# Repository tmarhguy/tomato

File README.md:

<h1 align="center">Tomato</h1>
<p align="center"><strong>A 32-bit computer architecture built from copper to browser.</strong></p>
<p align="center">

</p>

<p align="center">

</p>
<p align="center"><em>Physical ALU slice · <a href="web/assets/os/tomato-demo-os.mp4">FPGA Tomato OS recording (4× preview)</a></em></p>

The animation is a sped-up preview of the complete FPGA machine.

Tomato is one architecture expressed at several layers:

- a fabricated and soldered **8-bit 74xx Dual-LUT ALU slice**;
- a complete **FPGA Tomato** on the Nexys A7-100T that boots the
  assembly-written Tomato OS;
- **TOMATO OS v3.0**, written in Tomato assembly, with 14 menu entries;
- a functional **Virtual Tomato** ISA emulator in the browser;
- editable Digital schematics, KiCad boards, RTL, an assembler, and focused verification.

The complete discrete computer remains a goal. The assembled ALU slice is real
hardware, but it is not a complete discrete machine. The complete running
computer in this repository is the FPGA implementation.

**Explore:** [architecture](docs/architecture.md) ·
[current status](docs/status.md) ·
[Tomato OS](software/os/README.md) ·
[ISA](docs/isa/README.md) ·
[compute](docs/compute.md) ·
[documentation index](docs/README.md) ·
[project site](https://tomato.tmarhguy.com/)

## Architecture at a glance

These curated diagrams explain the system; the
[interactive GitDiagram](https://gitdiagram.com/tmarhguy/tomato) provides a
zoomable, generated map of the public repository's default branch.

**Visual entry points:** [interactive repository map](https://gitdiagram.com/tmarhguy/tomato) ·
[architecture guide](docs/architecture.md) ·
[web architecture](https://tomato.tmarhguy.com/architecture.html) ·
[ISA reference](https://tomato.tmarhguy.com/isa.html) ·
[run Virtual Tomato](https://tomato.tmarhguy.com/virtual.html)

### One architecture, several realizations

<picture>
  <source media="(prefers-color-scheme: dark)" srcset="web/assets/gallery/diagrams/system-realizations-dark.svg">
  
</picture>

The four realization boxes are deliberately separate. The assembled discrete
hardware proves the ALU slice; the FPGA is the complete machine; Icarus runs
the RTL locally; and the browser is a functional ISA emulator.
[Diagram source](docs/diagrams/system-realizations.mmd).

### From source files to runnable artifacts

<picture>
  <source media="(prefers-color-scheme: dark)" srcset="web/assets/gallery/diagrams/artifact-pipeline-dark.svg">
  
</picture>

The generated FPGA burn and browser image share the same OS and control data.
They do not share an execution engine: the FPGA and Icarus execute Verilog,
while `tomato-cpu.js` mirrors the ISA-level behavior in JavaScript.
[Diagram source](docs/diagrams/artifact-pipeline.mmd).

### Inside FPGA Tomato

<picture>
  <source media="(prefers-color-scheme: dark)" srcset="web/assets/gallery/diagrams/fpga-datapath-dark.svg">
  
</picture>

The board harness owns clocks, pins, keypad debounce, glyph rendering, DVI, and
seven-segment output. The machine core exposes those facilities as ports and
memory-mapped windows, keeping board-specific wiring outside the CPU RTL.
[Diagram source](docs/diagrams/fpga-datapath.mmd).

### Authority and state boundaries

- **Edit:** Digital schematics, ISA CSVs, assembly sources, and FPGA/browser
  implementation source.
- **Regenerate:** `.mem` images, `rtl/burn/*.vh`, `tomato-os.bin`, and
  bitstreams. These are derived artifacts, not design authorities.
- **Runtime state:** FPGA RAM, registers, framebuffer, compiler, radio mailbox,
  and the browser machine are volatile. Reset or reload restores the compiled
  image; this repository has no application database.
- **External systems:** Envelop clients, durable queues, hosted services, and
  the nearby bridge belong to the separate Envelop project.

## What runs now

| Layer | Current, repository-backed statement |
|---|---|
| Architecture | 32-bit datapath and instruction word |
| ALU | Custom three-source Dual-LUT ALU: two LUT3 functions feed an adder, `f(a,b,c) + g(a,b,c) + carry` |
| ISA | **91 instructions plus NOP, 92 burned rows** in a 512-row control ROM |
| Register array | Discrete (primary): **32,768 × 32-bit**. FPGA: **256 × 32-bit**, addressed as 3 bank bits plus a 5-bit register field; `r0` is hardwired to zero — no space for more on that implementation |
| FPGA | 100 MHz board input; **6.25 MHz** default CPU and 25 MHz pixel clocks; 90 MHz is only the nextpnr timing target |
| OS | The complete FPGA computer boots assembly-written **TOMATO OS v3.0**, with 14 menu entries including Envelop |
| Browser | Functional ISA-level emulation; not cycle-accurate RTL or physical execution |
| Hardware compiler | Counter FSM searches all **65,536 LUT pairs** for one fixed A/B/C/carry/output example; a hit verifies that example, not a general function |
| ALU verification | A **130-billion-vector** 32-bit ALU run is recorded and its harness is reproducible; the full run log is not checked in |

The architectural register count is **32,768**, because discrete is the
superior design constraint. FPGA implementation remains **256 × 32-bit**
because there is no space for a larger file; its 3-read/1-write array maps to
distributed RAM. Discrete uses external SRAM plus a seven-bit superbank and
`SETBANK2`. Neither the superbank nor that instruction exists in the current
FPGA RTL and burned ISA.

For evidence paths and the distinction between source-complete,
hardware-dependent, and deployed behavior, use
[`docs/status.md`](docs/status.md). Historical journal entries can describe
earlier designs and counts; they do not override current sources.

## See it, run it, inspect it

### Browser

Open the [Tomato site](https://tomato.tmarhguy.com/) and choose the Virtual
Tomato experience. Its checked-in OS image is generated from the assembly and
control data in this repository. Results there must be labeled virtual.

<p align="center">
  
</p>
<p align="center"><strong><a href="https://tomato.tmarhguy.com/virtual.html">Play with Virtual Tomato →</a></strong><br><em>Functional ISA emulation with simulated peripherals—not FPGA or discrete-hardware execution.</em></p>

### Local RTL simulation

Icarus Verilog can boot the OS and print its framebuffer without an FPGA:

```bash
make -C hardware/fpga/core os
```

Run the focused core regression:

```bash
make -C hardware/fpga/core test
```

These commands prove simulation behavior, not a currently programmed board.

### Assemble a Tomato program

```bash
python3 software/assembler.py software/asm/counter.s \
  -o /tmp/counter.mem --list
python3 software/assembler.py --selftest
```

The assembler reads the burned ISA and pseudo-instruction CSVs rather than
carrying a private opcode table.

### FPGA build

The default flow is Yosys → nextpnr-xilinx → Project X-Ray. An optional Linux
Vivado batch target is also provided. Building a bitstream does not prove that
a board is currently programmed.

```bash
make fpga-setup
make fpga
```

Programming is intentionally a separate, hardware-changing action; see
[`hardware/fpga/README.md`](hardware/fpga/README.md).

## Proof across the stack

<table>
  <tr>
    <td width="33%" align="center" valign="middle"></td>
    <td width="33%" align="center" valign="middle"></td>
    <td width="33%" align="center" valign="middle"></td>
  </tr>
</table>

- **Physical scope:** [`hardware/kicad/boards/07_alu/`](hardware/kicad/boards/07_alu/)
- **Editable logic:** [`hardware/digital/`](hardware/digital/)
- **Complete FPGA machine:** [`hardware/fpga/core/`](hardware/fpga/core/)
- **Machine software:** [`software/`](software/)
- **Verification:** [`verification/`](verification/)
- **Evidence and asset provenance:** [`docs/assets.md`](docs/assets.md)

## Envelop and compute

Envelop is a separate messaging project. Its Tomato-side client and bounded
compute executor are linked into Tomato OS; its user clients, backend, and
nearby bridge live outside this repository.

The intended hardware message path is:

`person → Envelop web app → backend queue → nearby verified bridge → Envelop in Tomato OS → Tomato CPU → labeled reply`

<picture>
  <source media="(prefers-color-scheme: dark)" srcset="web/assets/gallery/diagrams/envelop-boundary-dark.svg">
  
</picture>

Source in a repository is not evidence that a bridge is active or that a reply
ran on hardware. Bridge software is available in the separate Envelop project,
but a nearby authenticated bridge and completed FPGA job require live evidence.
Virtual previews are explicit, separate, and labeled. See
[`docs/compute.md`](docs/compute.md) for the current boundary.
[Diagram source](docs/diagrams/envelop-boundary.mmd).

## Repository map

| Path | Purpose |
|---|---|
| [`docs/`](docs/) | Canonical guides, ISA contracts, and historical journal |
| [`hardware/digital/`](hardware/digital/) | Editable architecture schematics |
| [`hardware/kicad/`](hardware/kicad/) | PCB designs and assembly records |
| [`hardware/fpga/`](hardware/fpga/) | Complete machine, board harness, and simulation |
| [`software/`](software/) | Assembler, programs, and Tomato OS |
| [`microcode/`](microcode/) | Control-ROM packaging |
| [`verification/`](verification/) | ALU and implementation checks |
| [`web/`](web/) | Project site and browser emulator |

## Documentation and history

Start with [`docs/README.md`](docs/README.md). It separates current canonical
guidance from the dated [`docs/log/`](docs/log/) engineering record. The
journal preserves decisions, wrong turns, and superseded designs as history;
use the [current journal index](docs/log/README.md) to navigate it.

Documentation authority and terminology are defined in
[`docs/documentation-policy.md`](docs/documentation-policy.md). When prose and
executable sources disagree, that policy determines which source wins.

## Documentation

Detailed architecture, implementation, verification, and technical
documentation is available in the project documentation.
The technical reference manual source is [`docs/index.adoc`](docs/index.adoc);
build the static manual locally with `make docs` (requires Asciidoctor).

## License and author

Tomato is licensed under the [Solderpad Hardware License 2.1](LICENSE).
Architecture and project by **Tyrone Marhguy**, Computer Engineering ’28,
University of Pennsylvania.

[Contributing](CONTRIBUTING.md) · [security](SECURITY.md) ·
[citation](CITATION.cff) · [third-party notices](THIRD_PARTY_NOTICES.md)

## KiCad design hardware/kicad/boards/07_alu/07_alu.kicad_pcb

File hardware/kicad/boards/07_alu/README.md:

# 07 — Dual-LUT ALU PCB

The physical **32-bit ALU** for Tomato — two independent 3-input LUT planes per bit, summed through **74ACT283** nibble adders, with on-board flag logic, carry select, and a bring-up LED wall. One PCB is an **8-bit slice**; stack two for 16-bit bench bring-up. Digital source of truth: [alu-32b-final.dig](../../../digital/modules/alu-32b-final.dig). KiCad project: [07_alu.kicad_pro](07_alu.kicad_pro).

<p align="center"><em>Lot 07 in the round &amp; on the iron · Dual-LUT slice</em></p>

---

## Table of Contents

- [At a glance](#at-a-glance)
- [Efficiency metrics](#efficiency-metrics)
- [Hierarchy](#hierarchy)
- [Schematics](#schematics)
- [PCB layout](#pcb-layout)
- [Bill of materials](#bill-of-materials)
- [I/O and bring-up](#io-and-bring-up)
- [Project files](#project-files)
- [Related docs](#related-docs)

---

## At a glance

```
alu_out[n] = ( lutA(a,b,c) + lutB(a,b,c) + cin ) & 1   per bit, ripple across nibbles
```

| Item | Detail |
|------|--------|
| Board | `07_alu` — modular 74xx ALU (not the legacy 270mm transistor `01_alu`) |
| Topology | `alu_1b_X` + `alu_1b_Y` → `alu_4b` × 2 (ripple carry) → 8b slice on PCB |
| Key ICs | **74ACT151** (LUT3 mux), **74ACT283** (4b adder), **74HCT688** (zero detect), **74ACT377** (flag reg), **74ACT541** (buffer) |
| Outline | **99.95 × 99.80 mm** ≈ **9975 mm²** (Edge.Cuts) |
| Density | **25 logic ICs / 8b** → **3.125 IC/bit**, **≈1247 mm²/bit** |
| Layout | Routed — **0 unrouted** nets (see status below) |
| Silk | Tomato ALU branding, UPenn / author contact on copper |

*Figure 1 — `07_alu` board render — `CELL 0` / `CELL 1`, flag logic, opcode/operand LED wall, I/O headers.*

*Figure 2 — Top copper — routed cells, flag block, silkscreen.*

---

## Efficiency metrics

| Metric | Value | Notes |
|--------|-------|-------|
| Board area | **99.95 × 99.80 mm** ≈ **9975 mm²** | Edge.Cuts bbox |
| Logic ICs (8b) | **25** | 17×151 + 2×283 + 2×00 + 1×86 + 1×377 + 1×541 + 1×688 |
| IC / bit | **3.125** | 25 / 8 |
| Board mm² / bit | **≈1247** | 9975 / 8 |

Legacy hybrid ([01_alu](../01_alu/README.md)): **3488 MOSFETs / 8b = 436 T/bit**. Journal carry-bypass ≈**16.5 MHz** on discrete path.

---

## Hierarchy

The KiCad tree mirrors the Digital verification ladder:

| Sheet | Role |
|-------|------|
| [07_alu.kicad_sch](07_alu.kicad_sch) | Top — two [alu_4b](alu_4b.kicad_sch) slices, `CIN-MAIN` / `COUT-MAIN` ripple |
| [alu_4b.kicad_sch](alu_4b.kicad_sch) | Four [alu_1b_X](alu_1b_X.kicad_sch) + four [alu_1b_Y](alu_1b_Y.kicad_sch) → one **74ACT283** |
| [alu_1b_X.kicad_sch](alu_1b_X.kicad_sch) / [alu_1b_Y.kicad_sch](alu_1b_Y.kicad_sch) | Single-bit **74ACT151** LUT3 (`lutA` / `lutB` programs via opcode buses) |
| [flags_logic.kicad_sch](flags_logic.kicad_sch) | Z/N/C/V, LT/GT/GTE, **74ACT151** carry select (`CSEL`) |
| [led_unit.kicad_sch](led_unit.kicad_sch) | Opcode, flag, and A/B/C/OUT bus LEDs for bench debug |
| [iopins.kicad_sch](iopins.kicad_sch) | Connector pinout — power, operands, opcodes, control |

Full CPU width is four 8-bit slices (or eight 4-bit cells) in the larger Tomato datapath; this board implements one **8-bit bring-up slice** with the same cell geometry used in simulation.

---

## Schematics

### Top sheet — two 4-bit ALU cells

*Figure 3 — `alu_4b_0` and `alu_4b_1` chained; `flags_logic`, `led_control`, and `iopins` sheets.*

### 4-bit slice — dual LUT into adder

*Figure 4 — `alu_1b_X0–X3` and `alu_1b_Y0–Y3` feed **U3 (74ACT283)**; `cinD` / `cout` nibble carry.*

### 1-bit LUT3 (`alu_1b_Y` example)

*Figure 5 — **74ACT151** as 3-input LUT: `a,b,c` select among `ALU_OPCODE_Y0–Y7`.*

### Flag logic

*Figure 6 — Zero compare (**74HCT688**), flag register (**74ACT377**), **74ACT151** `CIN-MAIN` mux from `CSEL` + latched flags.*

### LED bring-up panel

*Figure 7 — Visualize `ALU_OPCODE_X/Y`, flags, and A/B/C/OUT buses on the bench.*

### I/O connectors

*Figure 8 — Headers for A/B/C/OUT, opcode buses, `CSEL`, `FLAG_WE`, `SYS-CLK`, power.*

---

## PCB layout

| Asset | Description |
|-------|-------------|
| [alu_8b_board.webp](../../../../web/assets/pcb/alu_8b_board.webp) | Board render — assembled view, silk, LED wall |
| [alu_8b_pcb.jpg](../../../../web/assets/pcb/alu_8b_pcb.jpg) | 2D layout — top copper, cells, flag block |
| [status-bar.webp](../../../../web/assets/pcb/status-bar.webp) | Route status — **717 pads**, **358 vias**, **2405** segments, **185 nets**, **0 unrouted** |
| [drc.webp](../../../../web/assets/pcb/drc.webp) | Design Rules Check — **0 violations**, **0 unconnected** |

*Figure 9 — KiCad status bar — fully routed, fab-ready.*

*Figure 10 — DRC pass — no violations, no unconnected items.*

---

## Bill of materials

Each board is **131 placements** — mostly SOIC logic, a wall of 0805 LEDs, and a handful of through-hole resistor networks and headers. The tables below list **one board**; double quantities for a two-board 16-bit build.

### Integrated circuits

| Qty | Value | MPN (ordered) | Digi-Key | Role |
|-----|-------|---------------|----------|------|
| 17 | 74ACT151 | CD74ACT151M96 | [296-12766-1-ND](https://www.digikey.com/en/products/detail/texas-instruments/CD74ACT151M96/12766) | 8:1 mux — LUT3 planes in both cells + flag `CSEL` |
| 2 | 74ACT283 | CD74ACT283M | [296-32996-5-ND](https://www.digikey.com/en/products/detail/texas-instruments/CD74ACT283M/32996) | 4-bit ripple adder — one per nibble cell |
| 2 | 74ACT00 | SN74ACT00DR | [296-14690-1-ND](https://www.digikey.com/en/products/detail/texas-instruments/SN74ACT00DR/14690) | Quad NAND — glue in flag logic |
| 1 | 74ACT86 | SN74ACT86DR | [296-9757-1-ND](https://www.digikey.com/en/products/detail/texas-instruments/SN74ACT86DR/9757) | Quad XOR — flag compare |
| 1 | 74ACT377 | MC74ACT377DWR2G | [MC74ACT377DWR2GOSCT-ND](https://www.digikey.com/en/products/detail/onsemi/MC74ACT377DWR2G/377) | Octal D-FF — flag latch (U40) |
| 1 | 74ACT541 | CD74ACT541M96 | [296-14501-1-ND](https://www.digikey.com/en/products/detail/texas-instruments/CD74ACT541M96/14501) | Octal bus buffer (U1) |
| 1 | 74HC688 | CD74HCT688M96 | [296-24357-1-ND](https://www.digikey.com/en/products/detail/texas-instruments/CD74HCT688M96/24357) | 8-bit identity comparator — zero detect (U4); **HCT** for 5V ACT inputs |

### Passives and indicators

| Qty | Value | MPN (ordered) | Digi-Key | Footprint | Refs |
|-----|-------|---------------|----------|-----------|------|
| 25 | 100nF | CC0603KRX7R9BB104 | [311-1344-1-ND](https://www.digikey.com/en/products/detail/yageo/CC0603KRX7R9BB104/311) | 0603 | C3, C4, C16, C36–C59 |
| 63 | Red LED | LTST-C170KRKT | [160-1415-1-ND](https://www.digikey.com/en/products/detail/lite-on-inc/LTST-C170KRKT/160) | 0805 | D4–D71 |
| 7 | 470Ω bussed | 4610X-101-471LF | [4610X-1-471LF-ND](https://www.digikey.com/en/products/detail/bourns-inc/4610X-101-471LF/4610) | SIP-9 | RN1–RN7 |
| 2 | 470Ω bussed | 4604X-101-471LF | — | SIP-4 | RN9, RN10 |

The SIP-4 networks are **3-resistor bussed 470Ω** parts on [led_unit.kicad_sch](led_unit.kicad_sch). DigiKey often lists `4604X-101-471LF` on backorder with a high minimum — source from lab stock, or use **6× discrete 470Ω** per board (one end common, three to LED nets).

### Connectors

| Qty | Value | MPN | Refs |
|-----|-------|-----|------|
| 2 | 1×4 header | PRPC004SAAN-RC | J10, J11 |
| 7 | 1×8 header | PRPC008SAAN-RC | J5–J7, J12, J15–J17 |

Headers are standard 2.54 mm pin strips — any equivalent works.

### Ordering notes

- **DigiKey BOM (2 boards):** [`07_alu_digikey_bom.csv`](../../fabrication/07_alu/07_alu_digikey_bom.csv) — upload-ready CSV; order **`100884560`** placed Aug 2026 (~**$61** all-in for two boards).
- **Fabrication exports:** Gerbers, pick-and-place, and order receipt in [`hardware/kicad/fabrication/07_alu/`](../../fabrication/07_alu/).
- **PCBs:** JLCPCB bare boards — see [Ordered Tomato](../../../../docs/log/2026-08-07%20-%20Ordered%20Tomato.md).

---

## I/O and bring-up

From [iopins.kicad_sch](iopins.kicad_sch):

| Group | Signals |
|-------|---------|
| Operands | `A[7:0]`, `B[7:0]`, `C[7:0]` |
| Result | `OUT[7:0]` |
| LUT programs | `ALU_OPCODE_X0–X7`, `ALU_OPCODE_Y0–Y7` (8-bit truth table per LUT plane) |
| Carry select | `CSEL0–CSEL2` → `CIN-MAIN` |
| Flags | `FLAG_WE`, `ZIN`; outputs `flagZ/N/C/V`, LT/GT/GTE |
| Clock | `SYS-CLK` (flag register) |

Suggested flow: program opcode buses for a known LUT pair (e.g. add = `0x96` on both planes), wiggle operands on headers, read **OUT** on LEDs or scope — same spirit as [alu-display-control.dig](../../../digital/modules/alu-display-control.dig) on the full CPU.

---

## Project files

| File | Purpose |
|------|---------|
| [07_alu.kicad_pro](07_alu.kicad_pro) | KiCad project |
| [07_alu.kicad_sch](07_alu.kicad_sch) | Root schematic |
| [07_alu.kicad_pcb](07_alu.kicad_pcb) | PCB layout |
| [alu_1b_X.kicad_sch](alu_1b_X.kicad_sch), [alu_1b_Y.kicad_sch](alu_1b_Y.kicad_sch) | Bit slices |
| [alu_4b.kicad_sch](alu_4b.kicad_sch) | Nibble cell |
| [flags_logic.kicad_sch](flags_logic.kicad_sch), [led_unit.kicad_sch](led_unit.kicad_sch) | Status + debug |
| [iopins.kicad_sch](iopins.kicad_sch) | Connector map |
| [07_alu_digikey_bom.csv](../../fabrication/07_alu/07_alu_digikey_bom.csv) | DigiKey BOM — 2-board order |

Figures above live under [`web/assets/`](../../../../web/assets/).

---

## Related docs

| Doc | Topic |
|-----|-------|
| [Root README](../../../../README.md) | Project overview |
| [74251 carry mux log](../../../../docs/log/2026-06-26%20-%20ALU%20-%20Redesign%20with%2074251.md) | Why **74251/ACT151** over **74151** + tri-state |
| [Mode mux elimination](../../../../docs/log/2026-06-27%20-%20Elimination%20of%20Mode%20Multiplexers.md) | LUT3 feeds adder directly |
| [ALU segment display](../../../../docs/log/2026-06-19%20-%20ALU%20segment%20display%20design.md) | Display strategy on full CPU |
| [Ordered Tomato](../../../../docs/log/2026-08-07%20-%20Ordered%20Tomato.md) | PCB + parts order log |
| [First Phase of Assembly](../../../../docs/log/2026-08-18%20-%20First%20Phase%20of%20Assembly.md) | Muxes, adders, first lamps |
| [verification/README.md](../../../../verification/README.md) | Formal + UVM sign-off on Digital export |

**Author:** Tyrone Marhguy — see [Author](../../../../README.md#author) in root README.

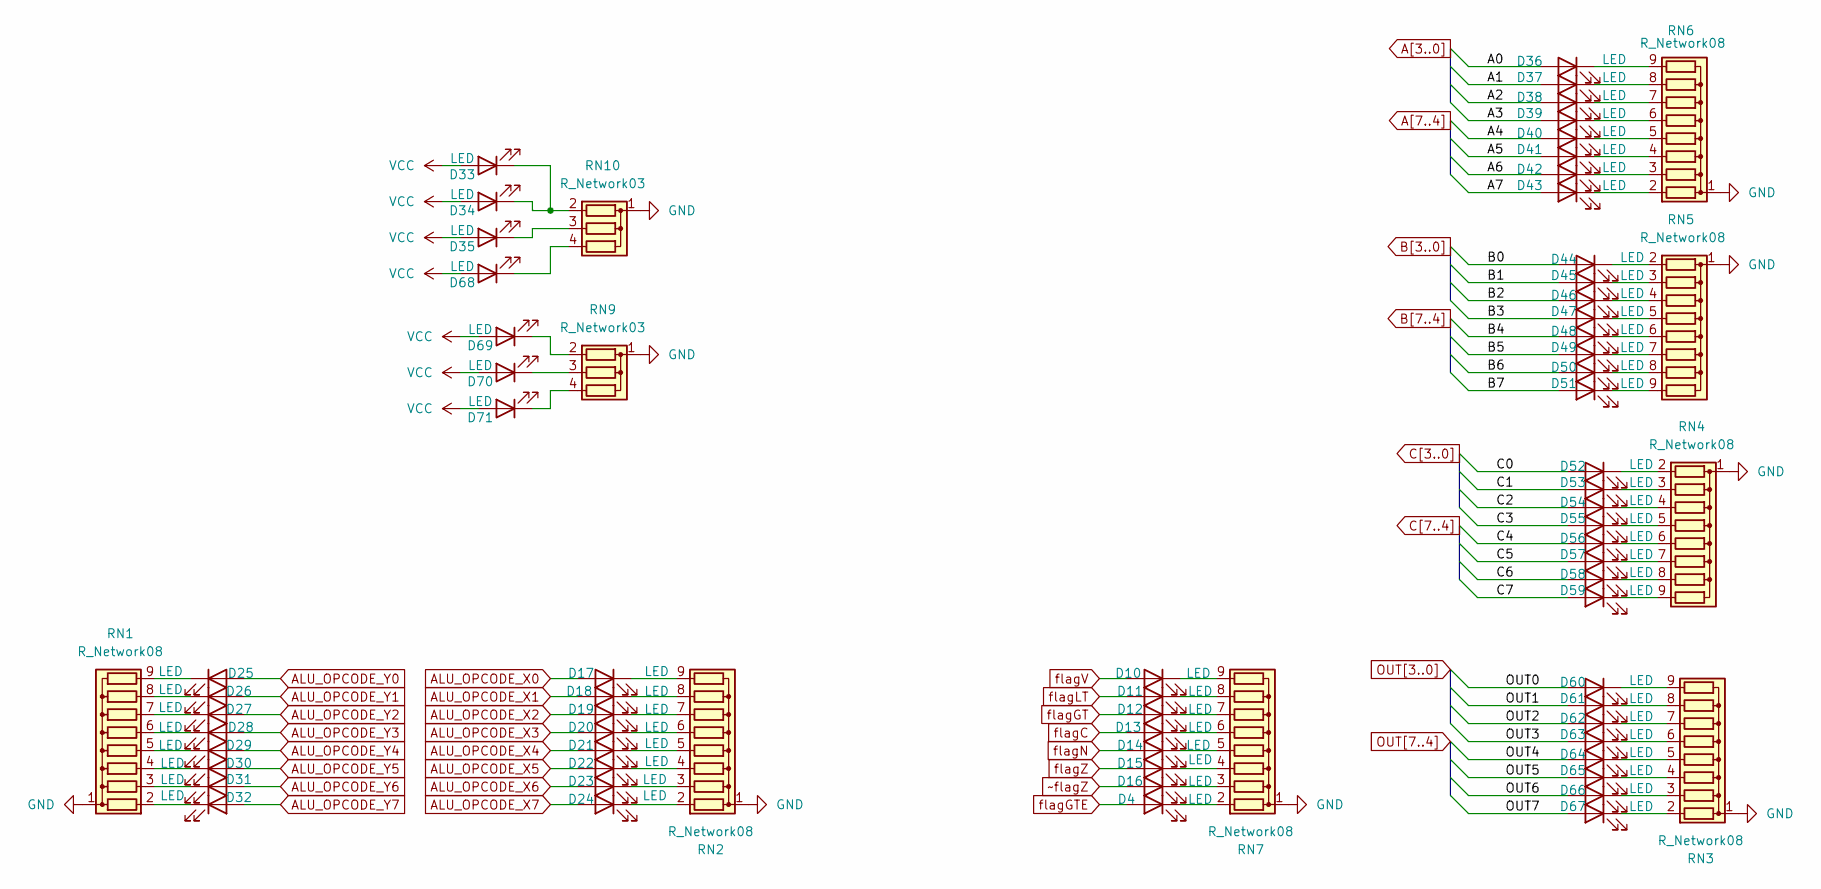
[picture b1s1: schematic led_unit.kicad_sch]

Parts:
D4, D10, D11, D12, D13, D14, D15, D16, D17, D18, D19, D20, D21, D22, D23, D24, D25, D26, D27, D28, D29, D30, D31, D32, D33, D34, D35, D36, D37, D38, D39, D40, D41, D42, D43, D44, D45, D46, D47, D48, D49, D50, D51, D52, D53, D54, D55, D56, D57, D58, D59, D60, D61, D62, D63, D64, D65, D66, D67, D68, D69, D70, D71: LED; LED_0805_2012Metric
RN1, RN2, RN3, RN4, RN5, RN6, RN7: R_Network08; R_Array_SIP9
RN9, RN10: R_Network03; R_Array_SIP4

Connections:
A0: D36.2 (A); also elsewhere on the board
A1: D37.2 (A); also elsewhere on the board
A2: D38.2 (A); also elsewhere on the board
A3: D39.2 (A); also elsewhere on the board
A4: D40.2 (A); also elsewhere on the board
A5: D41.2 (A); also elsewhere on the board
A6: D42.2 (A); also elsewhere on the board
A7: D43.2 (A); also elsewhere on the board
ALU_OPCODE_X0: D17.2 (A); also elsewhere on the board
ALU_OPCODE_X1: D18.2 (A); also elsewhere on the board
ALU_OPCODE_X2: D19.2 (A); also elsewhere on the board
ALU_OPCODE_X3: D20.2 (A); also elsewhere on the board
ALU_OPCODE_X4: D21.2 (A); also elsewhere on the board
ALU_OPCODE_X5: D22.2 (A); also elsewhere on the board
ALU_OPCODE_X6: D23.2 (A); also elsewhere on the board
ALU_OPCODE_X7: D24.2 (A); also elsewhere on the board
ALU_OPCODE_Y0: D25.2 (A); also elsewhere on the board
ALU_OPCODE_Y1: D26.2 (A); also elsewhere on the board
ALU_OPCODE_Y2: D27.2 (A); also elsewhere on the board
ALU_OPCODE_Y3: D28.2 (A); also elsewhere on the board
ALU_OPCODE_Y4: D29.2 (A); also elsewhere on the board
ALU_OPCODE_Y5: D30.2 (A); also elsewhere on the board
ALU_OPCODE_Y6: D31.2 (A); also elsewhere on the board
ALU_OPCODE_Y7: D32.2 (A); also elsewhere on the board
B0: D44.2 (A); also elsewhere on the board
B1: D45.2 (A); also elsewhere on the board
B2: D46.2 (A); also elsewhere on the board
B3: D47.2 (A); also elsewhere on the board
B4: D48.2 (A); also elsewhere on the board
B5: D49.2 (A); also elsewhere on the board
B6: D50.2 (A); also elsewhere on the board
B7: D51.2 (A); also elsewhere on the board
C0: D52.2 (A); also elsewhere on the board
C1: D53.2 (A); also elsewhere on the board
C2: D54.2 (A); also elsewhere on the board
C3: D55.2 (A); also elsewhere on the board
C4: D56.2 (A); also elsewhere on the board
C5: D57.2 (A); also elsewhere on the board
C6: D58.2 (A); also elsewhere on the board
C7: D59.2 (A); also elsewhere on the board
GND: RN1.1 (common), RN2.1 (common), RN3.1 (common), RN4.1 (common), RN5.1 (common), RN6.1 (common), RN7.1 (common), RN9.1 (common), RN10.1 (common); also elsewhere on the board
unnamed: D4.1 (K), RN7.2 (R1)
unnamed: D10.1 (K), RN7.9 (R8)
unnamed: D11.1 (K), RN7.8 (R7)
unnamed: D12.1 (K), RN7.7 (R6)
unnamed: D13.1 (K), RN7.6 (R5)
unnamed: D14.1 (K), RN7.5 (R4)
unnamed: D15.1 (K), RN7.4 (R3)
unnamed: D16.1 (K), RN7.3 (R2)
unnamed: D17.1 (K), RN2.9 (R8)
unnamed: D18.1 (K), RN2.8 (R7)
unnamed: D19.1 (K), RN2.7 (R6)
unnamed: D20.1 (K), RN2.6 (R5)
unnamed: D21.1 (K), RN2.5 (R4)
unnamed: D22.1 (K), RN2.4 (R3)
unnamed: D23.1 (K), RN2.3 (R2)
unnamed: D24.1 (K), RN2.2 (R1)
unnamed: D25.1 (K), RN1.9 (R8)
unnamed: D26.1 (K), RN1.8 (R7)
unnamed: D27.1 (K), RN1.7 (R6)
unnamed: D28.1 (K), RN1.6 (R5)
unnamed: D29.1 (K), RN1.5 (R4)
unnamed: D30.1 (K), RN1.4 (R3)
unnamed: D31.1 (K), RN1.3 (R2)
unnamed: D32.1 (K), RN1.2 (R1)
unnamed: D33.1 (K), D34.1 (K), RN10.2 (R1)
unnamed: D35.1 (K), RN10.3 (R2)
unnamed: D36.1 (K), RN6.9 (R8)
unnamed: D37.1 (K), RN6.8 (R7)
unnamed: D38.1 (K), RN6.7 (R6)
unnamed: D39.1 (K), RN6.6 (R5)
unnamed: D40.1 (K), RN6.5 (R4)
unnamed: D41.1 (K), RN6.4 (R3)
unnamed: D42.1 (K), RN6.3 (R2)
unnamed: D43.1 (K), RN6.2 (R1)
unnamed: D44.1 (K), RN5.2 (R1)
unnamed: D45.1 (K), RN5.3 (R2)
unnamed: D46.1 (K), RN5.4 (R3)
unnamed: D47.1 (K), RN5.5 (R4)
unnamed: D48.1 (K), RN5.6 (R5)
unnamed: D49.1 (K), RN5.7 (R6)
unnamed: D50.1 (K), RN5.8 (R7)
unnamed: D51.1 (K), RN5.9 (R8)
unnamed: D52.1 (K), RN4.2 (R1)
unnamed: D53.1 (K), RN4.3 (R2)
unnamed: D54.1 (K), RN4.4 (R3)
unnamed: D55.1 (K), RN4.5 (R4)
unnamed: D56.1 (K), RN4.6 (R5)
unnamed: D57.1 (K), RN4.7 (R6)
unnamed: D58.1 (K), RN4.8 (R7)
unnamed: D59.1 (K), RN4.9 (R8)
unnamed: D60.1 (K), RN3.9 (R8)
unnamed: D61.1 (K), RN3.8 (R7)
unnamed: D62.1 (K), RN3.7 (R6)
unnamed: D63.1 (K), RN3.6 (R5)
unnamed: D64.1 (K), RN3.5 (R4)
unnamed: D65.1 (K), RN3.4 (R3)
unnamed: D66.1 (K), RN3.3 (R2)
unnamed: D67.1 (K), RN3.2 (R1)
unnamed: D68.1 (K), RN10.4 (R3)
unnamed: D69.1 (K), RN9.2 (R1)
unnamed: D70.1 (K), RN9.3 (R2)
unnamed: D71.1 (K), RN9.4 (R3)
OUT0: D60.2 (A); also elsewhere on the board
OUT1: D61.2 (A); also elsewhere on the board
OUT2: D62.2 (A); also elsewhere on the board
OUT3: D63.2 (A); also elsewhere on the board
OUT4: D64.2 (A); also elsewhere on the board
OUT5: D65.2 (A); also elsewhere on the board
OUT6: D66.2 (A); also elsewhere on the board
OUT7: D67.2 (A); also elsewhere on the board
VCC: D33.2 (A), D34.2 (A), D35.2 (A), D68.2 (A), D69.2 (A), D70.2 (A), D71.2 (A); also elsewhere on the board
flagC: D13.2 (A); also elsewhere on the board
flagGT: D12.2 (A); also elsewhere on the board
flagGTE: D4.2 (A); also elsewhere on the board
flagLT: D11.2 (A); also elsewhere on the board
flagN: D14.2 (A); also elsewhere on the board
flagV: D10.2 (A); also elsewhere on the board
flagZ: D15.2 (A); also elsewhere on the board
~flagZ: D16.2 (A); also elsewhere on the board

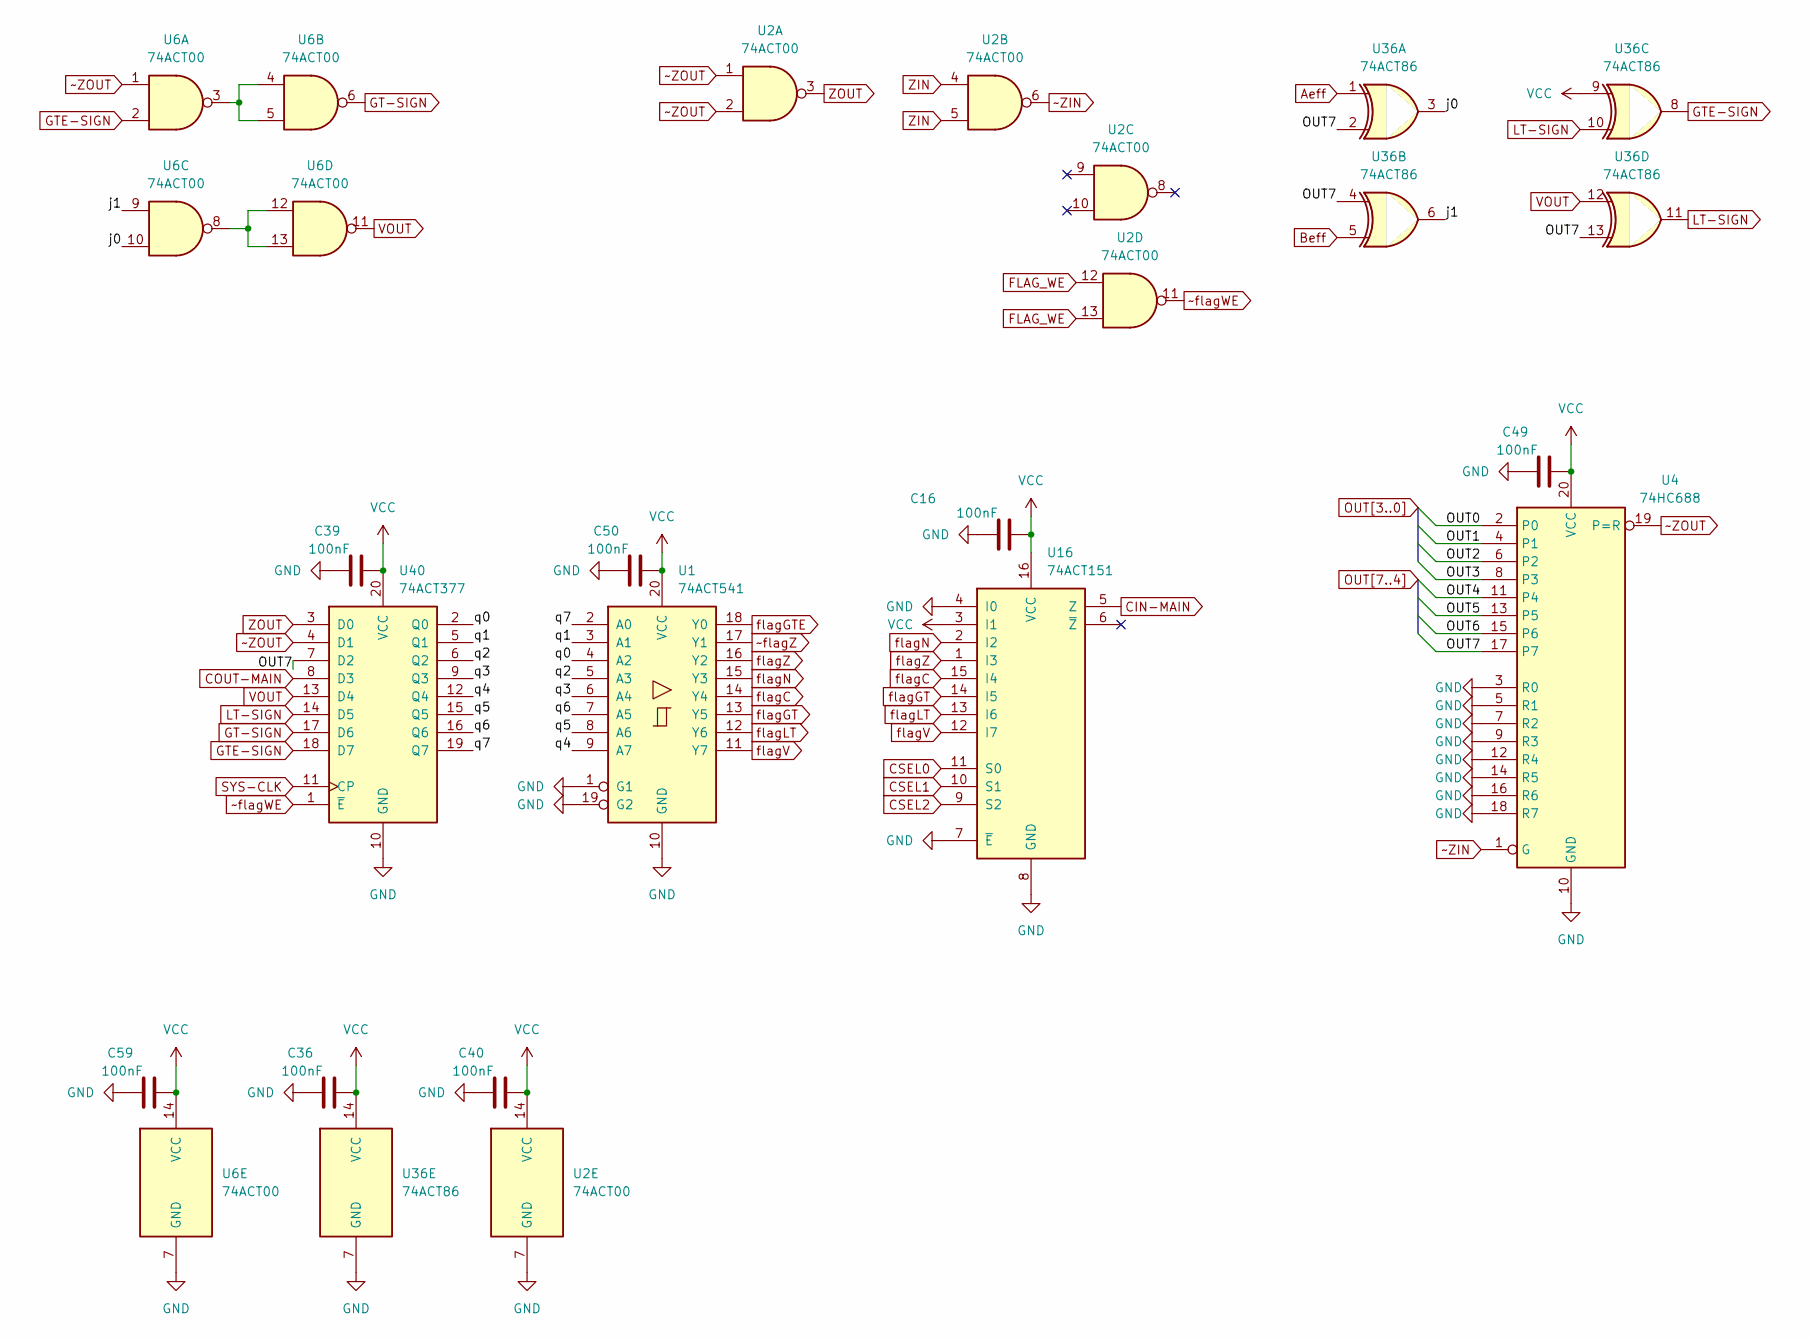
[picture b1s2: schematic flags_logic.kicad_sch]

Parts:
C16, C36, C39, C40, C49, C50, C59: 100nF; C_0603_1608Metric
U1: 74ACT541; SOIC-20W_7.5x12.8mm_P1.27mm
U2, U6: 74ACT00; SOIC-14_3.9x8.7mm_P1.27mm
U4: 74HC688; SOIC-20W_7.5x12.8mm_P1.27mm
U16: 74ACT151; SOIC-16_3.9x9.9mm_P1.27mm
U36: 74ACT86; SOIC-14_3.9x8.7mm_P1.27mm
U40: 74ACT377; SOIC-20W_7.5x12.8mm_P1.27mm

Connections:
/flags_logic/j0: U6.10, U36.3
/flags_logic/j1: U6.9, U36.6
/flags_logic/q0: U1.4 (A2), U40.2 (Q0)
/flags_logic/q1: U1.3 (A1), U40.5 (Q1)
/flags_logic/q2: U1.5 (A3), U40.6 (Q2)
/flags_logic/q3: U1.6 (A4), U40.9 (Q3)
/flags_logic/q4: U1.9 (A7), U40.12 (Q4)
/flags_logic/q5: U1.8 (A6), U40.15 (Q5)
/flags_logic/q6: U1.7 (A5), U40.16 (Q6)
/flags_logic/q7: U1.2 (A0), U40.19 (Q7)
Aeff: U36.1; also elsewhere on the board
Beff: U36.5; also elsewhere on the board
CIN-MAIN: U16.5 (Z); also elsewhere on the board
COUT-MAIN: U40.8 (D3); also elsewhere on the board
CSEL0: U16.11 (S0); also elsewhere on the board
CSEL1: U16.10 (S1); also elsewhere on the board
CSEL2: U16.9 (S2); also elsewhere on the board
FLAG_WE: U2.12, U2.13; also elsewhere on the board
GND: C16.1, C36.1, C39.1, C40.1, C49.1, C50.1, C59.1, U1.1 (G1), U1.10 (GND), U1.19 (G2), U2.7 (GND), U4.3 (R0), U4.5 (R1), U4.7 (R2), U4.9 (R3), U4.10 (GND), U4.12 (R4), U4.14 (R5), U4.16 (R6), U4.18 (R7), U6.7 (GND), U16.4 (I0), U16.7 (~E), U16.8 (GND), U36.7 (GND), U40.10 (GND); also elsewhere on the board
GT-SIGN: U6.6, U40.17 (D6)
GTE-SIGN: U6.2, U36.8, U40.18 (D7)
LT-SIGN: U36.10, U36.11, U40.14 (D5)
unnamed: U6.3, U6.4, U6.5
unnamed: U6.8, U6.12, U6.13
OUT0: U4.2 (P0); also elsewhere on the board
OUT1: U4.4 (P1); also elsewhere on the board
OUT2: U4.6 (P2); also elsewhere on the board
OUT3: U4.8 (P3); also elsewhere on the board
OUT4: U4.11 (P4); also elsewhere on the board
OUT5: U4.13 (P5); also elsewhere on the board
OUT6: U4.15 (P6); also elsewhere on the board
OUT7: U4.17 (P7), U36.2, U36.4, U36.13, U40.7 (D2); also elsewhere on the board
SYS-CLK: U40.11 (CP); also elsewhere on the board
VCC: C16.2, C36.2, C39.2, C40.2, C49.2, C50.2, C59.2, U1.20 (VCC), U2.14 (VCC), U4.20 (VCC), U6.14 (VCC), U16.3 (I1), U16.16 (VCC), U36.9, U36.14 (VCC), U40.20 (VCC); also elsewhere on the board
VOUT: U6.11, U36.12, U40.13 (D4)
ZIN: U2.4, U2.5; also elsewhere on the board
ZOUT: U2.3, U40.3 (D0)
flagC: U1.14 (Y4), U16.15 (I4); also elsewhere on the board
flagGT: U1.13 (Y5), U16.14 (I5); also elsewhere on the board
flagGTE: U1.18 (Y0); also elsewhere on the board
flagLT: U1.12 (Y6), U16.13 (I6); also elsewhere on the board
flagN: U1.15 (Y3), U16.2 (I2); also elsewhere on the board
flagV: U1.11 (Y7), U16.12 (I7); also elsewhere on the board
flagZ: U1.16 (Y2), U16.1 (I3); also elsewhere on the board
~ZIN: U2.6, U4.1 (G)
~ZOUT: U2.1, U2.2, U4.19 (P=R), U6.1, U40.4 (D1)
~flagWE: U2.11, U40.1 (~E)
~flagZ: U1.17 (Y1); also elsewhere on the board

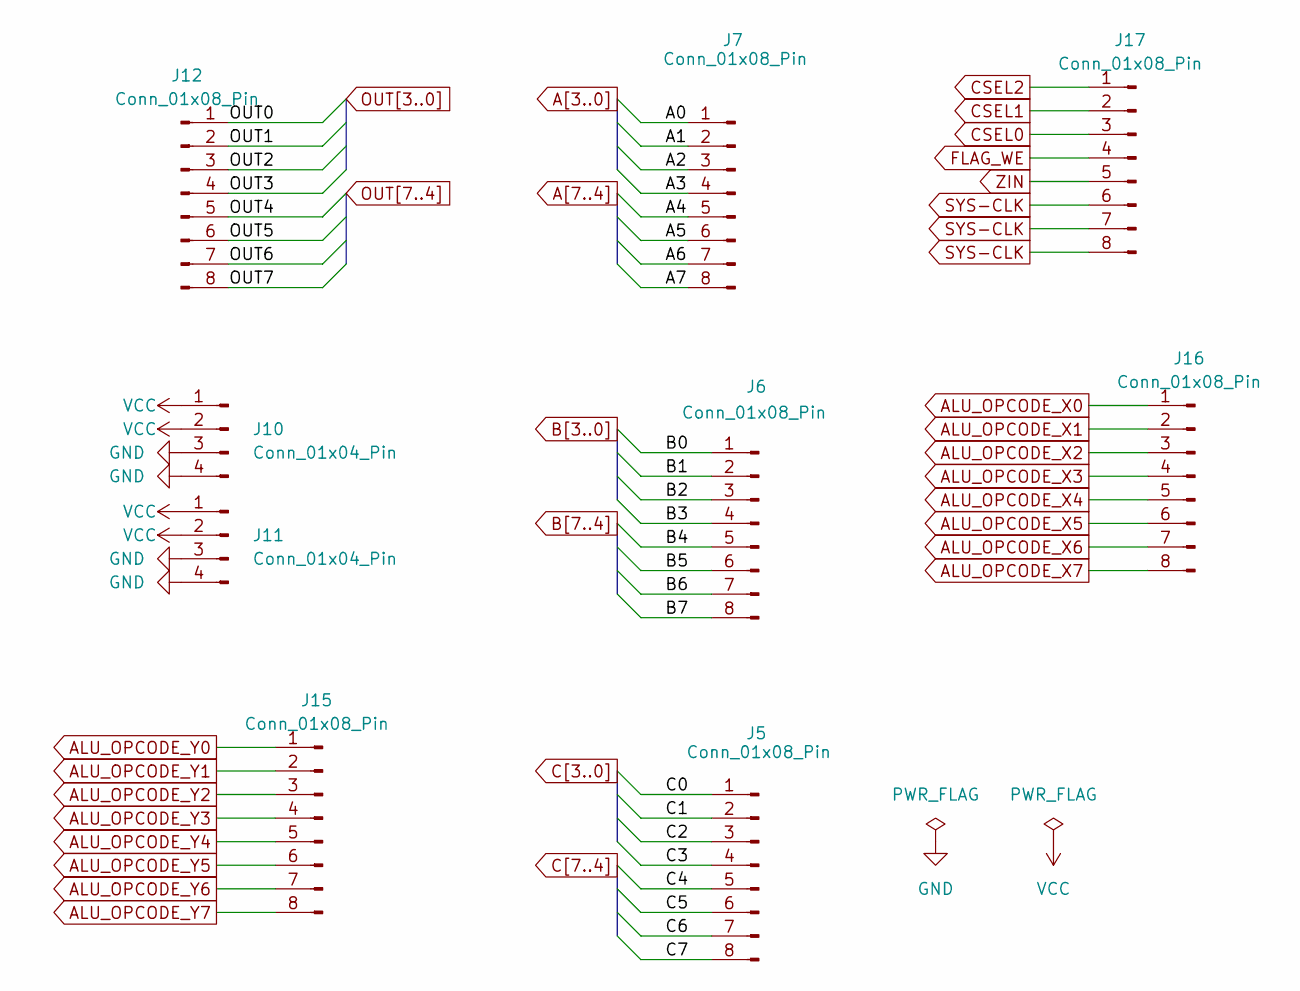
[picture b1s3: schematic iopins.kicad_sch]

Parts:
J5, J6, J7, J12, J15, J16, J17: Conn_01x08_Pin; PinHeader_1x08_P2.54mm_Vertical
J10, J11: Conn_01x04_Pin; PinHeader_1x04_P2.54mm_Vertical

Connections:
A0: J7.1; also elsewhere on the board
A1: J7.2; also elsewhere on the board
A2: J7.3; also elsewhere on the board
A3: J7.4; also elsewhere on the board
A4: J7.5; also elsewhere on the board
A5: J7.6; also elsewhere on the board
A6: J7.7; also elsewhere on the board
A7: J7.8; also elsewhere on the board
ALU_OPCODE_X0: J16.1; also elsewhere on the board
ALU_OPCODE_X1: J16.2; also elsewhere on the board
ALU_OPCODE_X2: J16.3; also elsewhere on the board
ALU_OPCODE_X3: J16.4; also elsewhere on the board
ALU_OPCODE_X4: J16.5; also elsewhere on the board
ALU_OPCODE_X5: J16.6; also elsewhere on the board
ALU_OPCODE_X6: J16.7; also elsewhere on the board
ALU_OPCODE_X7: J16.8; also elsewhere on the board
ALU_OPCODE_Y0: J15.1; also elsewhere on the board
ALU_OPCODE_Y1: J15.2; also elsewhere on the board
ALU_OPCODE_Y2: J15.3; also elsewhere on the board
ALU_OPCODE_Y3: J15.4; also elsewhere on the board
ALU_OPCODE_Y4: J15.5; also elsewhere on the board
ALU_OPCODE_Y5: J15.6; also elsewhere on the board
ALU_OPCODE_Y6: J15.7; also elsewhere on the board
ALU_OPCODE_Y7: J15.8; also elsewhere on the board
B0: J6.1; also elsewhere on the board
B1: J6.2; also elsewhere on the board
B2: J6.3; also elsewhere on the board
B3: J6.4; also elsewhere on the board
B4: J6.5; also elsewhere on the board
B5: J6.6; also elsewhere on the board
B6: J6.7; also elsewhere on the board
B7: J6.8; also elsewhere on the board
C0: J5.1; also elsewhere on the board
C1: J5.2; also elsewhere on the board
C2: J5.3; also elsewhere on the board
C3: J5.4; also elsewhere on the board
C4: J5.5; also elsewhere on the board
C5: J5.6; also elsewhere on the board
C6: J5.7; also elsewhere on the board
C7: J5.8; also elsewhere on the board
CSEL0: J17.3; also elsewhere on the board
CSEL1: J17.2; also elsewhere on the board
CSEL2: J17.1; also elsewhere on the board
FLAG_WE: J17.4; also elsewhere on the board
GND: J10.3, J10.4, J11.3, J11.4; also elsewhere on the board
OUT0: J12.1; also elsewhere on the board
OUT1: J12.2; also elsewhere on the board
OUT2: J12.3; also elsewhere on the board
OUT3: J12.4; also elsewhere on the board
OUT4: J12.5; also elsewhere on the board
OUT5: J12.6; also elsewhere on the board
OUT6: J12.7; also elsewhere on the board
OUT7: J12.8; also elsewhere on the board
SYS-CLK: J17.6, J17.7, J17.8; also elsewhere on the board
VCC: J10.1, J10.2, J11.1, J11.2; also elsewhere on the board
ZIN: J17.5; also elsewhere on the board

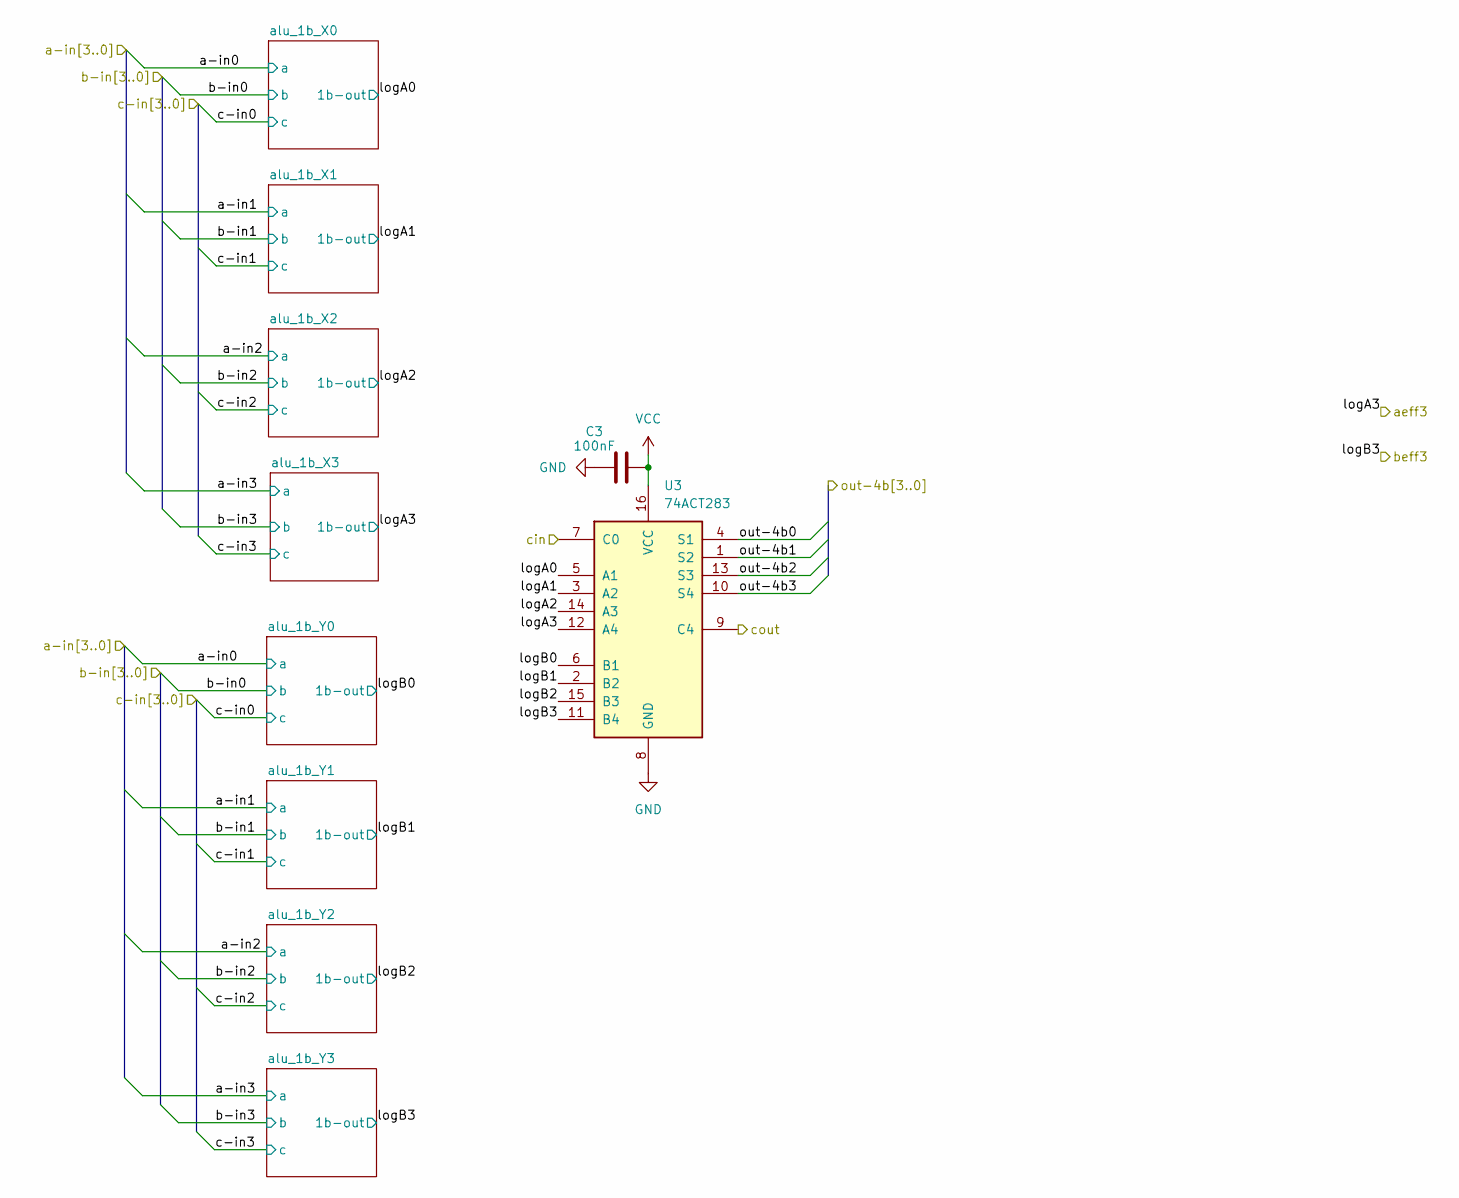
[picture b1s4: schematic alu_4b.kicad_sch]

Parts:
C3: 100nF; C_0603_1608Metric
U3: 74ACT283; SOIC-16_3.9x9.9mm_P1.27mm

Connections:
/alu_4b_0/cout: U3.9 (C4); also elsewhere on the board
/alu_4b_0/logA0: U3.5 (A1); also elsewhere on the board
/alu_4b_0/logA1: U3.3 (A2); also elsewhere on the board
/alu_4b_0/logA2: U3.14 (A3); also elsewhere on the board
/alu_4b_0/logA3: U3.12 (A4); also elsewhere on the board
/alu_4b_0/logB0: U3.6 (B1); also elsewhere on the board
/alu_4b_0/logB1: U3.2 (B2); also elsewhere on the board
/alu_4b_0/logB2: U3.15 (B3); also elsewhere on the board
/alu_4b_0/logB3: U3.11 (B4); also elsewhere on the board
CIN-MAIN: U3.7 (C0); also elsewhere on the board
GND: C3.1, U3.8 (GND); also elsewhere on the board
OUT0: U3.4 (S1); also elsewhere on the board
OUT1: U3.1 (S2); also elsewhere on the board
OUT2: U3.13 (S3); also elsewhere on the board
OUT3: U3.10 (S4); also elsewhere on the board
VCC: C3.2, U3.16 (VCC); also elsewhere on the board

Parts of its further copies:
C4: 100nF; C_0603_1608Metric
U5: 74ACT283; SOIC-16_3.9x9.9mm_P1.27mm

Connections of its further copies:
/alu_4b_0/cout: U5.7 (C0); also elsewhere on the board
/alu_4b_1/logA0: U5.5 (A1); also elsewhere on the board
/alu_4b_1/logA1: U5.3 (A2); also elsewhere on the board
/alu_4b_1/logA2: U5.14 (A3); also elsewhere on the board
/alu_4b_1/logB0: U5.6 (B1); also elsewhere on the board
/alu_4b_1/logB1: U5.2 (B2); also elsewhere on the board
/alu_4b_1/logB2: U5.15 (B3); also elsewhere on the board
Aeff: U5.12 (A4); also elsewhere on the board
Beff: U5.11 (B4); also elsewhere on the board
COUT-MAIN: U5.9 (C4); also elsewhere on the board
GND: C4.1, U5.8 (GND); also elsewhere on the board
OUT4: U5.4 (S1); also elsewhere on the board
OUT5: U5.1 (S2); also elsewhere on the board
OUT6: U5.13 (S3); also elsewhere on the board
OUT7: U5.10 (S4); also elsewhere on the board
VCC: C4.2, U5.16 (VCC); also elsewhere on the board

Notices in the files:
README.md:
License: SHL-2.1
